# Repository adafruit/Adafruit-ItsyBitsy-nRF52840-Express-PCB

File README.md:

## Adafruit ItsyBitsy nRF52840 Express PCB

<a href="http://www.adafruit.com/products/4481"><br/>
Click here to purchase one from the Adafruit shop</a>

PCB files for the Adafruit ItsyBitsy nRF52840 Express. 

Format is EagleCAD schematic and board layout
* https://www.adafruit.com/product/4481

### Description

What's smaller than a Feather but larger than a Trinket? It's an Adafruit ItsyBitsy nRF52840 Express featuring the Nordic nRF52840 Bluetooth LE processor! Teensy & powerful, with an fast nRF52840 Cortex M4 processor running at 64 MHz and 1 MB of FLASH - this microcontroller board is perfect when you want something very compact, with a heap-load of memory and Bluetooth LE support This Itsy is your best option for tiny wireless connectivity - it can act as both a BLE central and peripheral, with support in both Arduino and CircuitPython

ItsyBitsy nRF52840 Express is only 1.4" long by 0.7" wide, but has 6 power pins, 21 digital GPIO pins (6 of which can be analog in). It's the same chip as the Feather nRF52840 but really really small. So it's great for thse really compact builds. It even comes with 2MB of QSPI Flash built in, for data logging, file storage, or CircuitPython code.

The most exciting part of the ItsyBitsy is that while we ship it with an Arduino IDE compatible demo, you can also install CircuitPython on board with only a few clicks. When you plug it in, it will show up as a very small disk drive with code.py on it. Edit code.py with your favorite text editor to build your wireless-enabled project using Python, the most popular programming language. No installs, IDE or compiler needed, so you can use it on any computer, even ChromeBooks or computers you can't install software on. When you're done, unplug the Itsy' and your code will go with you.

Here are some of the updates you can look forward to when using ItsyBitsy nRF52:

* Same size, form-factor as the remaining ItsyBitsy mainboards - with a similar but not identical pinout (there's no pins at the end of the board like most other Itsy's due to the radio antenna being there.
* Floating point support with Cortex M4 DSP instructions
* 32-bit, 3.3V logic and power with power/enable pin
* 1024 KB flash, 256 KB RAM
* 2 MB QSPI FLASH chip for storing files and CircuitPython code storage.
* Native Open Source USB stack - pre-programmed with UF2 bootloader
* Bluetooth Low Energy compatible 2.4GHz radio (Details available in the nRF52840 product specification)
* FCC / IC / TELEC certified module
* Up to +8dBm output power
* 21 GPIO, 6 x 12-bit ADC pins, up to 12 PWM outputs (3 PWM modules with 4 outputs each)
* Red LED for general purpose blinking, mini DotStar RGB LED for colorful feedback
* 1 x Special Vhigh output pin gives you the higher voltage from VBAT or VUSB, for driving NeoPixels, servos, and other 5V-logic devices. Digital 5 level-shifted output for high-voltage logic level output.
* Native USB supported by every OS - can be used in Arduino or CircuitPython as USB serial console, Keyboard/Mouse HID, even a little disk drive for storing Python scripts.
* Can be used with Arduino IDE or CircuitPython
* Comes pre-loaded with the UF2 bootloader, which looks like a USB storage key. Simply drag firmware on to program, no special tools or drivers needed! It can be used to load up CircuitPython or Arduino IDE

Each order comes with one assembled and tested ItsyBitsy nRF52840, with headers that can be soldered in for use with a breadboard.

So what are you waiting for? Pick up a ItsyBitsy nRF today and be amazed at how easy and fast it is to get started with the teensiest  Bluetooth dev board we have.

### License

Adafruit invests time and resources providing this open source design, please support Adafruit and open-source hardware by purchasing products from [Adafruit](https://www.adafruit.com)!

Designed by Limor Fried/Ladyada for Adafruit Industries.

Creative Commons Attribution/Share-Alike, all text above must be included in any redistribution. 
See license.txt for additional details.

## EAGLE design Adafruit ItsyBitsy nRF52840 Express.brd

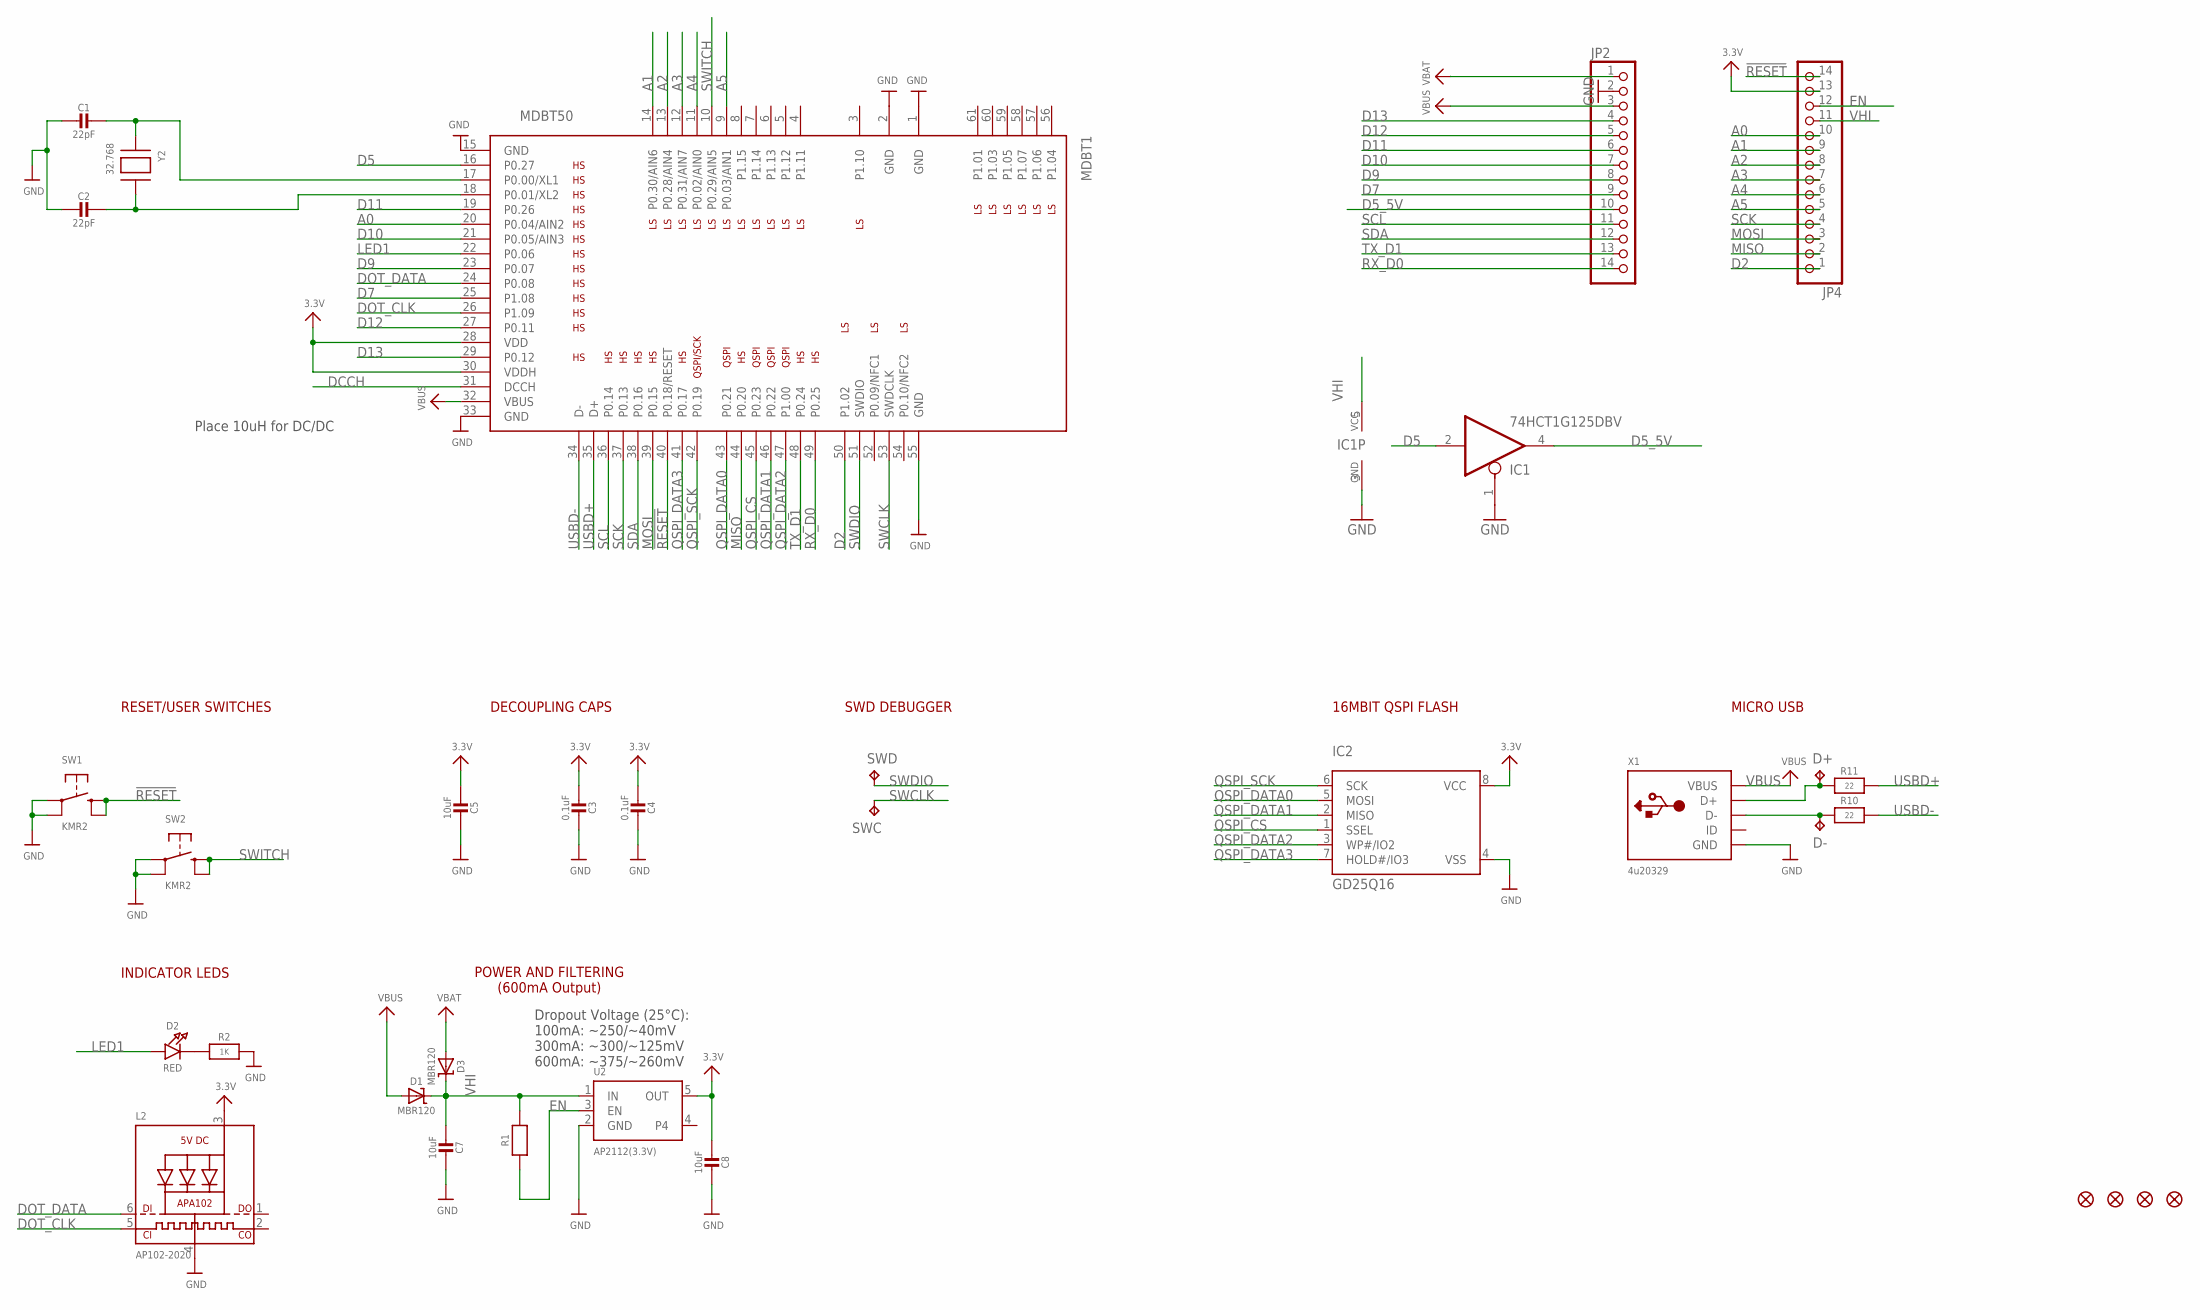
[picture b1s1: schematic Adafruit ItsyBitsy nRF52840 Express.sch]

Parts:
C1, C2: 22pF; _0603MP
C3, C4: 0.1uF; 0603-NO
C5, C7, C8: 10uF; 0805-NO
D1, D3: MBR120; SOD-123
D2: RED; CHIPLED_0805_NOOUTLINE
D+: TPTP10R; TP10R
D-: TPTP10R; TP10R
FID1, FID2, FID3, FID4: FIDUCIAL_1MM
IC1: 74HCT1G125DBV; SOT23-5
IC2: GD25Q16; USON8
JP2, JP4: HEADER-1X14; 1X14_ROUND70
L2: AP102-2020; APA102_2020
MDBT1: MDBT50
R1: 10K; 0603-NO
R2: 1K; 0603-NO
R10, R11: 22; 0603-NO
SW1, SW2: KMR2; BTN_KMR2_4.6X2.8
SWC: TPTP13R; TP13R
SWD: TPTP13R; TP13R
U2: AP2112(3.3V); SOT23-5
X1: 4u20329; 4UCONN_20329_V2
Y2: 32.768; XTAL3215

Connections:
3.3V: C3.2, C4.2, C5.2, C8.2, IC2.8 (VCC), JP4.13, L2.3 (VDD), MDBT1.28 (VDD), MDBT1.30 (VDDH), U2.5 (OUT)
!RESET: JP4.14, MDBT1.40 (P0.18/RESET), SW1.B (S), SW1.B' (S1)
A0: JP4.10, MDBT1.20 (P0.04/AIN2)
A1: JP4.9, MDBT1.14 (P0.30/AIN6)
A2: JP4.8, MDBT1.13 (P0.28/AIN4)
A3: JP4.7, MDBT1.12 (P0.31/AIN7)
A4: JP4.6, MDBT1.11 (P0.02/AIN0)
A5: JP4.5, MDBT1.9 (P0.03/AIN1)
D2: JP4.1, MDBT1.50 (P1.02)
D5: IC1.2 (I), MDBT1.16 (P0.27)
D5_5V: IC1.4 (O), JP2.10
D7: JP2.9, MDBT1.25 (P1.08)
D9: JP2.8, MDBT1.23 (P0.07)
D10: JP2.7, MDBT1.21 (P0.05/AIN3)
D11: JP2.6, MDBT1.19 (P0.26)
D12: JP2.5, MDBT1.27 (P0.11)
D13: JP2.4, MDBT1.29 (P0.12)
D+: D+.TP, R11.1, X1.D+
D-: D-.TP, R10.1, X1.D-
DCCH: MDBT1.31 (DCCH)
DOT_CLK: L2.5 (CKI), MDBT1.26 (P1.09)
DOT_DATA: L2.6 (DI), MDBT1.24 (P0.08)
EN: JP4.12, R1.1, U2.3 (EN)
GND: C1.2, C2.2, C3.1, C4.1, C5.1, C7.1, C8.1, IC1.1 (OE), IC1.3 (GND), IC2.4 (VSS), JP2.2, L2.4 (GND), MDBT1.1 (GND), MDBT1.2 (GND), MDBT1.15 (GND), MDBT1.33 (GND), MDBT1.55 (GND), R2.2, SW1.A, SW1.A' (P1), SW2.A, SW2.A' (P1), U2.2 (GND), X1.BASE@1 (GND), X1.BASE@2 (GND), X1.GND, X1.SPRT@1 (GND), X1.SPRT@2 (GND), X1.SPRT@3 (GND), X1.SPRT@4 (GND)
LED1: D2.A, MDBT1.22 (P0.06)
MISO: JP4.2, MDBT1.44 (P0.20)
MOSI: JP4.3, MDBT1.39 (P0.15)
unnamed: D2.C, R2.1
unnamed: C1.1, MDBT1.17 (P0.00/XL1), Y2.P$1
unnamed: C2.1, MDBT1.18 (P0.01/XL2), Y2.P$2
QSPI_CS: IC2.1 (SSEL), MDBT1.45 (P0.23)
QSPI_DATA0: IC2.5 (MOSI), MDBT1.43 (P0.21)
QSPI_DATA1: IC2.2 (MISO), MDBT1.46 (P0.22)
QSPI_DATA2: IC2.3 (WP#/IO2), MDBT1.47 (P1.00)
QSPI_DATA3: IC2.7 (HOLD#/IO3), MDBT1.41 (P0.17)
QSPI_SCK: IC2.6 (SCK), MDBT1.42 (P0.19)
RX_D0: JP2.14, MDBT1.49 (P0.25)
SCK: JP4.4, MDBT1.37 (P0.13)
SCL: JP2.11, MDBT1.36 (P0.14)
SDA: JP2.12, MDBT1.38 (P0.16)
SWCLK: MDBT1.53 (SWDCLK), SWC.TP
SWDIO: MDBT1.51 (SWDIO), SWD.TP
SWITCH: MDBT1.10 (P0.29/AIN5), SW2.B (S), SW2.B' (S1)
TX_D1: JP2.13, MDBT1.48 (P0.24)
USBD+: MDBT1.35 (D+), R11.2
USBD-: MDBT1.34 (D-), R10.2
VBAT: D3.A, JP2.1
VBUS: D1.A, JP2.3, MDBT1.32 (VBUS), X1.VBUS
VHI: C7.2, D1.C, D3.C, IC1.5 (VCC), JP4.11, R1.2, U2.1 (IN)

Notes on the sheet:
POWER AND FILTERING (600mA Output)
Dropout Voltage (25°C): 100mA: ~250/~40mV 300mA: ~300/~125mV 600mA: ~375/~260mV
INDICATOR LEDS
RESET/USER SWITCHES
DECOUPLING CAPS
SWD DEBUGGER
16MBIT QSPI FLASH
MICRO USB
Place 10uH for DC/DC

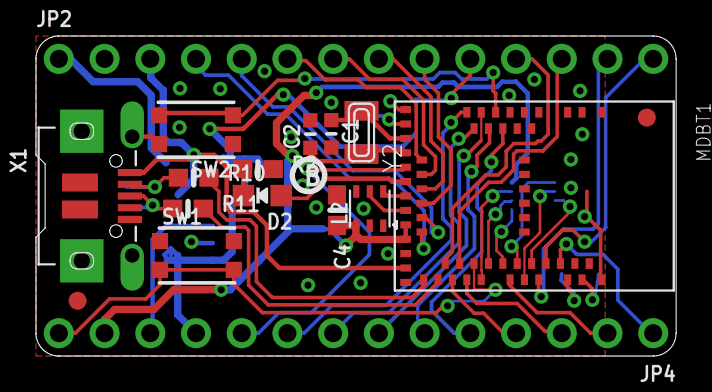
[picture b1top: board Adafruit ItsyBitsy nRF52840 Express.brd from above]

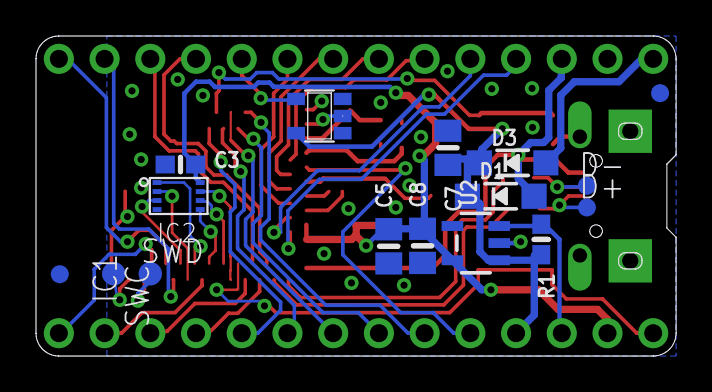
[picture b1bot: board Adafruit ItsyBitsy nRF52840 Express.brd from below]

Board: 2 copper layers, 35.6 x 17.8 mm, 36 parts (17 on the bottom side), 48 nets.

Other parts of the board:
U$12: ITSYNRF52840_TOP
U$14: ITSYNRF52840_BOT
U$15: PCBFEAT-REV-040

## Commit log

2020-01-27 Adding board files.
2021-05-15 Add pin reference PDF

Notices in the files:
parts and their libraries:
microbuilder: This work is placed in the public domain, and may be freely used for commercial and non-commercial work with the following conditions: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
